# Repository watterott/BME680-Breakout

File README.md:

# BME680-Breakout
Breakout with BME680 Digital Environmental Sensor from Bosch Sensortec.

* [Bosch BME680](https://www.bosch-sensortec.com/bst/products/all_products/bme680) Integrated Environmental Sensor (Air Quality, Humidity, Pressure and Temperature)
* Temperature Sensor -40...85°C
* Pressure Sensor 300...1100hPa (+9000...-500m above/below sea level)
* Humidity Sensor 0...100%
* Gas Sensor for Air Quality (IAQ)
* On-board 3.3V voltage regulator
* SPI Interface (up to 10MHz)
* TWI/I2C Interface (address 0x76 when SDO=0 or 0x77 when SDO=1, CS=1 for I2C)
* 3.3V - 5V Power Supply and Logic Level
* Open-Source and released under the [Creative Commons Attribution Share-Alike License](https://creativecommons.org/licenses/by-sa/4.0/).
* **[Documentation on learn.watterott.com](https://learn.watterott.com)**

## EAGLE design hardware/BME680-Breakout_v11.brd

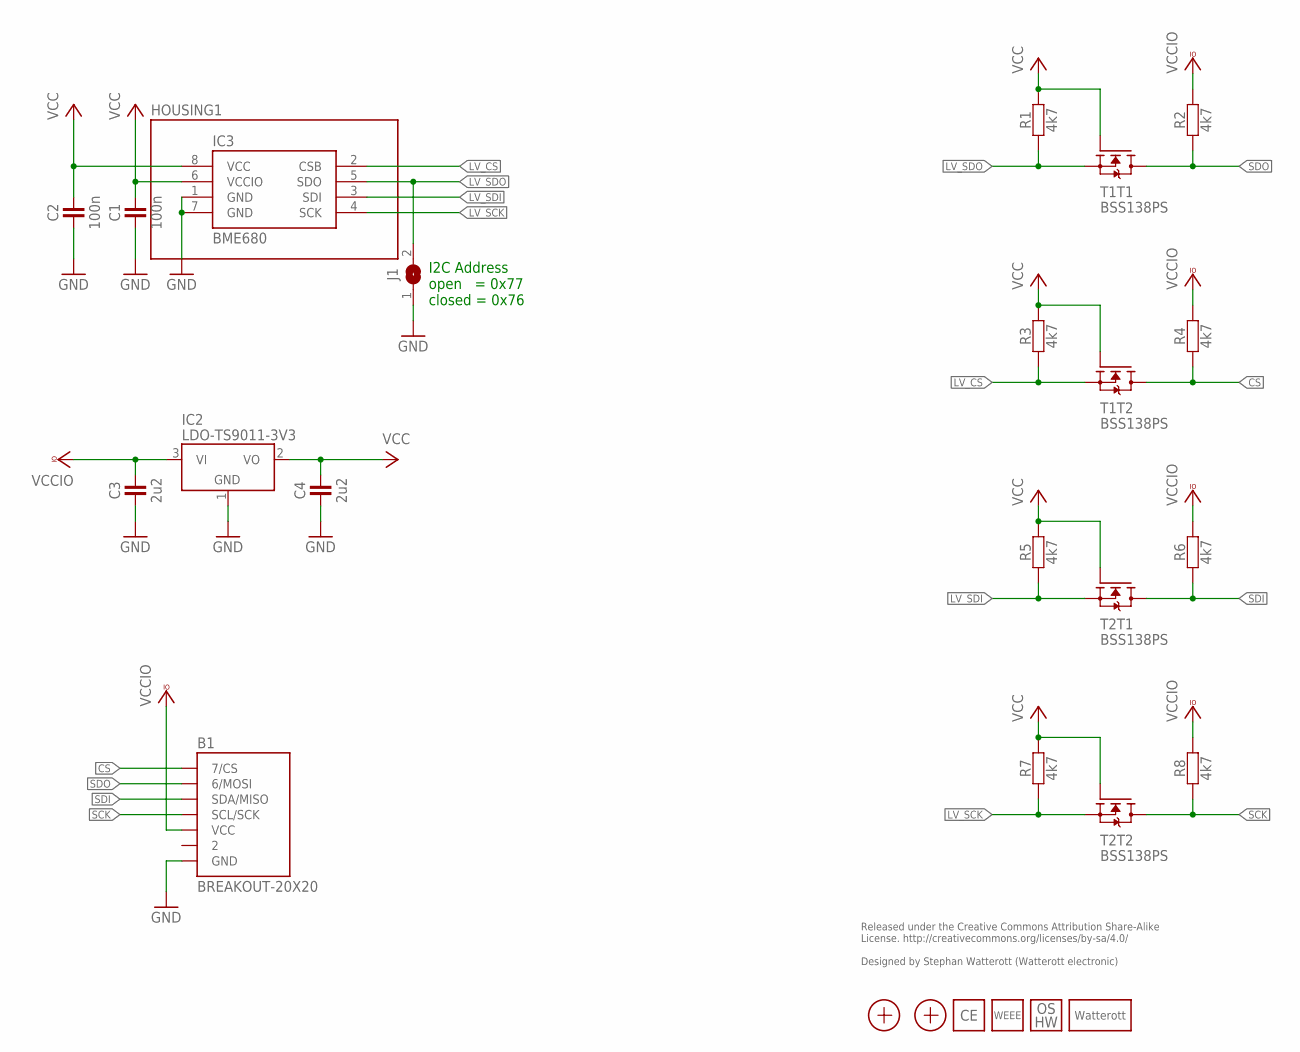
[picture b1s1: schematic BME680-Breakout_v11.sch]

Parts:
B1: BREAKOUT-20X20
C1, C2: 100n; C0402
C3, C4: 2u2; C0402
HOUSING1: SF2
IC2: LDO-TS9011-3V3; SOT23
IC3: BME680
J1: JUMPER2-0603
LOGO3: LOGO_CE-2; CE_2MM
LOGO4: LOGO_WEEE-4; WEEE_4MM
LOGO5: LOGO_OSHW-2; OSHW_2MM
LOGO6: LOGO_SPARK-2; SPARK_2MM
R1, R2, R3, R4, R5, R6, R7, R8: 4k7; C0402
T1, T2: BSS138PS; SOT363
X1, X2: PASSER-07; PASSER_07MM

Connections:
CS: B1.CS (7/CS), R4.1, T1.3 (D)
GND: B1.GND, C1.1, C2.1, C3.1, C4.1, IC2.1 (GND), IC3.1 (GND), IC3.7 (GND), J1.1
LV_CS: IC3.2 (CSB), R3.1, T1.4 (S)
LV_SCK: IC3.4 (SCK), R7.1, T2.4 (S)
LV_SDI: IC3.3 (SDI), R5.1, T2.1 (S)
LV_SDO: IC3.5 (SDO), J1.2, R1.1, T1.1 (S)
SCK: B1.SCL/SCK, R8.1, T2.3 (D)
SDI: B1.SDA/MISO, R6.1, T2.6 (D)
SDO: B1.MOSI (6/MOSI), R2.1, T1.6 (D)
VCC: C1.2, C2.2, C4.2, IC2.2 (VO), IC3.6 (VCCIO), IC3.8 (VCC), R1.2, R3.2, R5.2, R7.2, T1.2 (G), T1.5 (G), T2.2 (G), T2.5 (G)
VCCIO: B1.VCC, C3.2, IC2.3 (VI), R2.2, R4.2, R6.2, R8.2

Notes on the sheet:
I2C Address open = 0x77 closed = 0x76
Released under the Creative Commons Attribution Share-Alike License. http://creativecommons.org/licenses/by-sa/4.0/ Designed by Stephan Watterott (Watterott electronic)

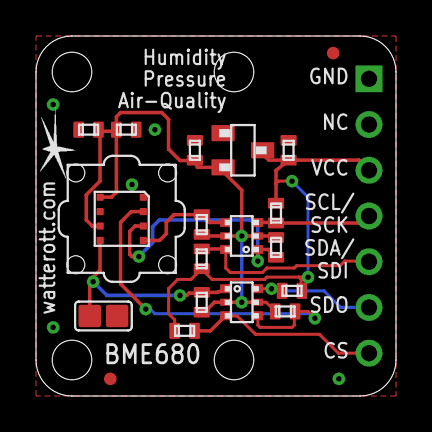
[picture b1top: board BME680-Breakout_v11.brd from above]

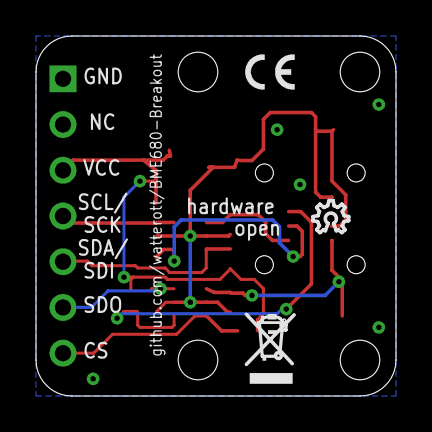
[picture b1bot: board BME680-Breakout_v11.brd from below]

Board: 2 copper layers, 20.0 x 20.0 mm, 25 parts (3 on the bottom side), 11 nets.

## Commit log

2017-09-12 updated layout and schematic
2018-05-01 added rev 1.1
